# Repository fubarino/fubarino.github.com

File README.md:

fubarino: Social Hardware and Software
========
Main Project Pages are:
http://fubarino.org

The chipKIT Fubarino SD board brings affordable, breadboard compatible high speed computing power to the Arduino-compatible chipKIT/MPIDE platform. It is able to run almost all Arduino sketches right out of the box at a great price, and includes more memory, speed, and I/O pins than a typical Arduino or clone. And it includes a microSD card slot for easy sketch access to huge file storage.
chipKIT FubarinoSD
======
Class on a stick. Course materials can fit on the SD card. The device mounts as a USB device. Unfortunately, at 1.0 speeds. But 
it will cut 45 minutes of getting started to 15 minutes. When offering online course using electronics all the course materials can be placed on the board.

The goal with the project is two have two boards that are excellent for small, and bread boardable projects.

Social Hardware:
=====
* Open Source
* Open Hardware
* Sharable

Licensing
====
The chipKIT Fubarino SD hardware is licensed under the Solderpad Hardware License v0.5. All MPIDE source code is licensed under GPL or other open source software licenses.

Availability:
========
These boards are Open Source Hardware and all the files are managed in this project, and are licensed as OpenSource.

* Purchase Fubarino SD version 1.5 at [microchipDIRECT](http://www.microchipdirect.com/ProductSearch.aspx?Keywords=TCHIP010)
* Purchase Fubarino SD version 1.4 at [Seeed Studio](http://www.seeedstudio.com/depot/fubarino-sd-p-1265.html?cPath=132_133)
* Purchase Fubarino Mini version 1.5 at [microchipDIRECT](http://www.microchipdirect.com/ProductSearch.aspx?Keywords=TCHIP011)

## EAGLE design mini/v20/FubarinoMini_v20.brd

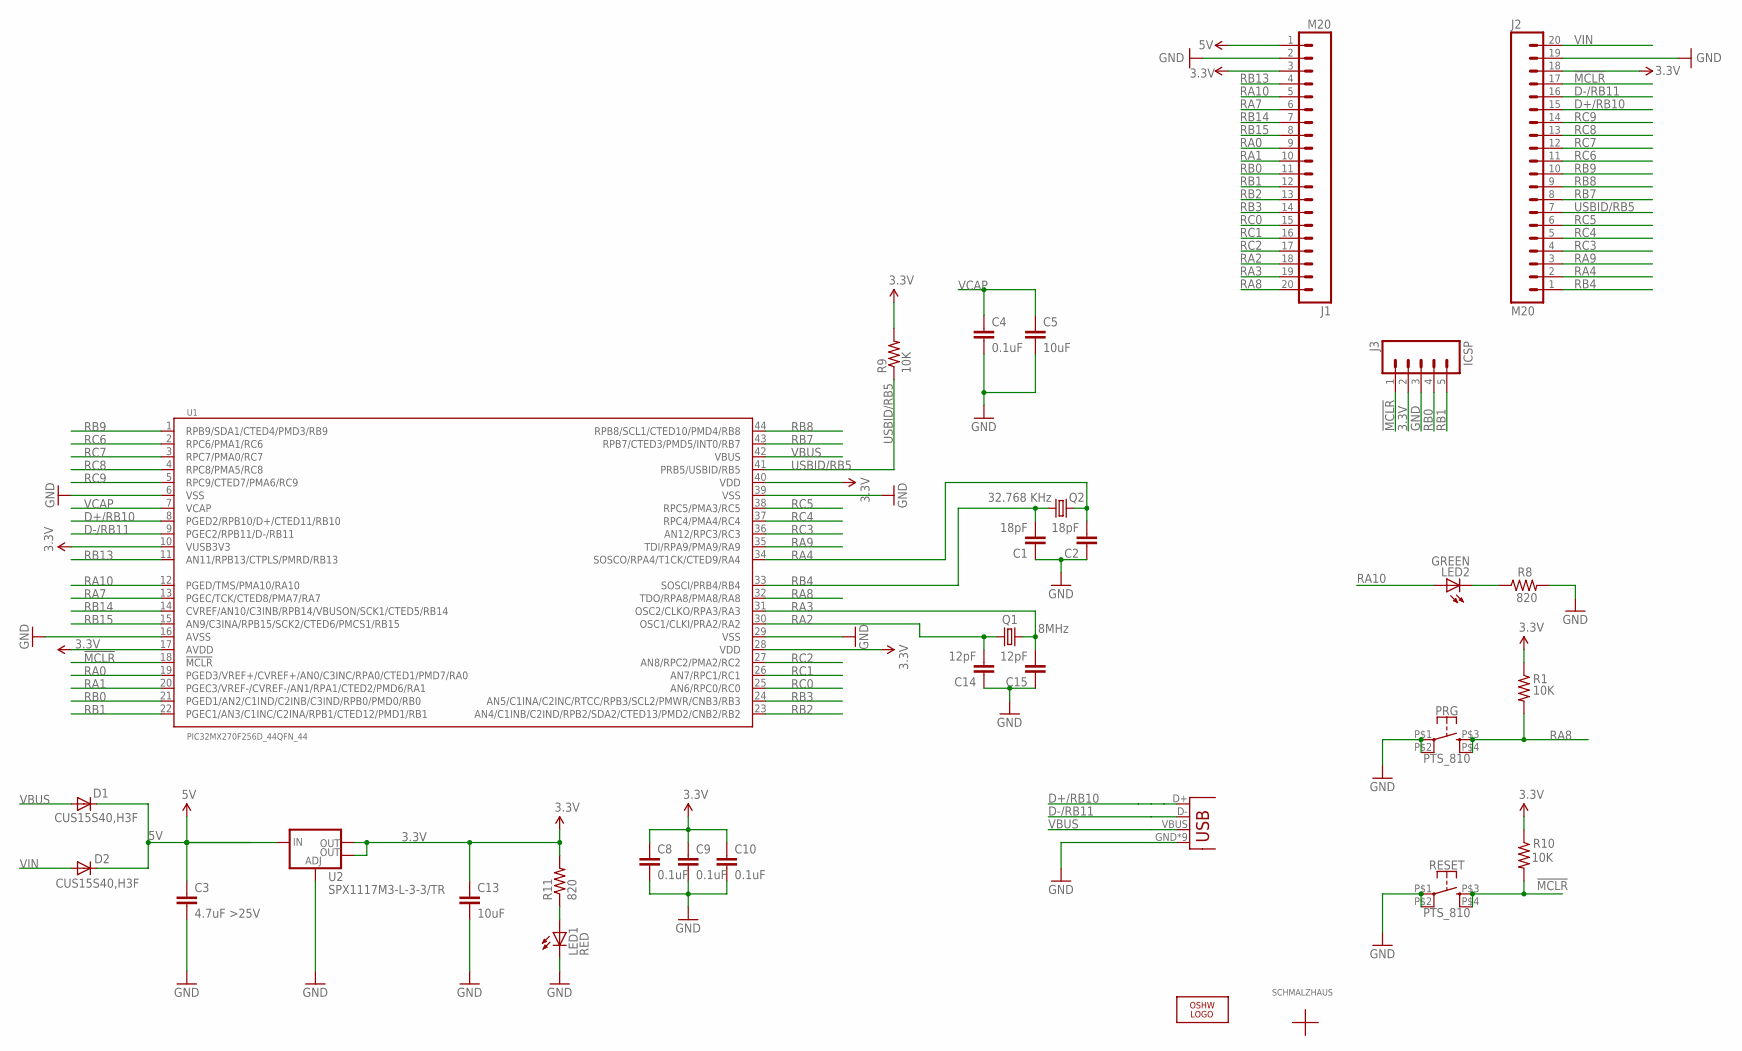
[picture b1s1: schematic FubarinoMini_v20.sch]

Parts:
C1, C2: 18pF; 0603-CAP
C3: 4.7uF >25V; 0603-CAP
C4, C8, C9: 0.1uF; 0603-CAP
C5, C13: 10uF; 0805
C10: 0.1uF; 0603
C14, C15: 12pF; 0603-CAP
D1, D2: CUS15S40,H3F; SOD-323
ICSP: J3; 1X05_NOSILK
J1, J2: M20; 1X20_NO_PIN1
LED1: RED; LED-0603
LED2: GREEN; LED-0603
LOGO1: OSHW_LOGO_8MILX0070-NT; OSHW_8X70_NOTEXT
PRG: PTS_810
Q1: 8MHz; NX3225GD
Q2: 32.768 KHz; TC26H
R1, R9, R10: 10K; 0603-RES
R8, R11: 820; 0603-RES
RESET: PTS_810
U1: PIC32MX270F256D_44QFN_44; QFN-44-8X8-NOPAD
U2: SPX1117M3-L-3-3/TR; SOT223
U$1: SCHMALZHAUSSCHMALZHAUS_SMALL; SCHMALZHAUS_SMALL
U$2: CE_MARK5MM; CE_5MM
U$3: ROSH_GARBAGE; ROHS_GARBAGE_5MM
U$4: CHIPKIT2MM; CHIPKIT_2MM
U$5: USBMICROB; USB-MICROB_FCI_PINS

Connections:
3.3V: C8.1, C9.1, C10.1, C13.1, ICSP.2, J1.3, J2.18, R1.1, R9.2, R10.1, R11.2, U1.10 (VUSB3V3), U1.17 (AVDD), U1.28 (VDD), U1.40 (VDD), U2.2 (OUT), U2.4 (OUT)
5V: C3.1, D1.1 (C), D2.1 (C), J1.1, U2.3 (IN)
!MCLR!: ICSP.1, J2.17, R10.2, RESET.P$3 (3), RESET.P$4 (4), U1.18 (!MCLR!)
D+/RB10: J2.15, U1.8 (PGED2/RPB10/D+/CTED11/RB10), U$5.D+
D-/RB11: J2.16, U1.9 (PGEC2/RPB11/D-/RB11), U$5.D-
GND: C1.1, C2.1, C3.2, C4.2, C5.2, C8.2, C9.2, C10.2, C13.2, C14.1, C15.1, ICSP.3, J1.2, J2.19, LED1.C, PRG.P$1 (1), PRG.P$2 (2), R8.2, RESET.P$1 (1), RESET.P$2 (2), U1.6 (VSS), U1.16 (AVSS), U1.29 (VSS), U1.39 (VSS), U2.1 (ADJ), U$5.GND, U$5.GND@1 (GND), U$5.GND@2 (GND), U$5.GND@3 (GND), U$5.GND@4 (GND), U$5.GND@5 (GND), U$5.GND@6 (GND), U$5.GND@7 (GND), U$5.GND@8 (GND)
unnamed: LED1.A, R11.1
unnamed: LED2.C, R8.1
RA0: J1.9, U1.19 (PGED3/VREF+/CVREF+/AN0/C3INC/RPA0/CTED1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)
RA1: J1.10, U1.20 (PGEC3/VREF-/CVREF-/AN1/RPA1/CTED2/PMD6/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)
RA2: C14.2, J1.18, Q1.P$1 (1), U1.30 (OSC1/CLKI/PRA2/RA2)
RA3: C15.2, J1.19, Q1.P$2 (2), U1.31 (OSC2/CLKO/RPA3/RA3)
RA4: C2.2, J2.2, Q2.1, U1.34 (SOSCO/RPA4/T1CK/CTED9/RA4)
RA7: J1.6, U1.13 (PGEC/TCK/CTED8/PMA7/RA7)
RA8: J1.20, PRG.P$3 (3), PRG.P$4 (4), R1.2, U1.32 (TDO/RPA8/PMA8/RA8)
RA9: J2.3, U1.35 (TDI/RPA9/PMA9/RA9)
RA10: J1.5, LED2.A, U1.12 (PGED/TMS/PMA10/RA10)
RB0: ICSP.4, J1.11, U1.21 (PGED1/AN2/C1IND/C2INB/C3IND/RPB0/PMD0/R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)
RB1: ICSP.5, J1.12, U1.22 (PGEC1/AN3/C1INC/C2INA/RPB1/CTED12/PMD1/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)
RB2: J1.13, U1.23 (AN4/C1INB/C2IND/RPB2/SDA2/CTED13/PMD2/C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)
RB3: J1.14, U1.24 (AN5/C1INA/C2INC/RTCC/RPB3/SCL2/PMWR/CNB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)
RB4: C1.2, J2.1, Q2.2, U1.33 (SOSCI/PRB4/RB4)
RB7: J2.8, U1.43 (RPB7/CTED3/PMD5/INT0/RB7)
RB8: J2.9, U1.44 (RPB8/SCL1/CTED10/PMD4/RB8)
RB9: J2.10, U1.1 (RPB9/SDA1/CTED4/PMD3/RB9)
RB13: J1.4, U1.11 (AN11/RPB13/CTPLS/PMRD/RB13)
RB14: J1.7, U1.14 (CVREF/AN10/C3INB/RPB14/VBUSON/SCK1/CTED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)
RB15: J1.8, U1.15 (AN9/C3INA/RPB15/SCK2/CTED6/PMCS1/RB15)
RC0: J1.15, U1.25 (AN6/RPC0/RC0)
RC1: J1.16, U1.26 (AN7/RPC1/RC1)
RC2: J1.17, U1.27 (AN8/RPC2/PMA2/RC2)
RC3: J2.4, U1.36 (AN12/RPC3/RC3)
RC4: J2.5, U1.37 (RPC4/PMA4/RC4)
RC5: J2.6, U1.38 (RPC5/PMA3/RC5)
RC6: J2.11, U1.2 (RPC6/PMA1/RC6)
RC7: J2.12, U1.3 (RPC7/PMA0/RC7)
RC8: J2.13, U1.4 (RPC8/PMA5/RC8)
RC9: J2.14, U1.5 (RPC9/CTED7/PMA6/RC9)
USBID/RB5: J2.7, R9.1, U1.41 (PRB5/USBID/RB5)
VBUS: D1.2 (A), U1.42 (VBUS), U$5.VBUS
VCAP: C4.1, C5.1, U1.7 (VCAP)
VIN: D2.2 (A), J2.20

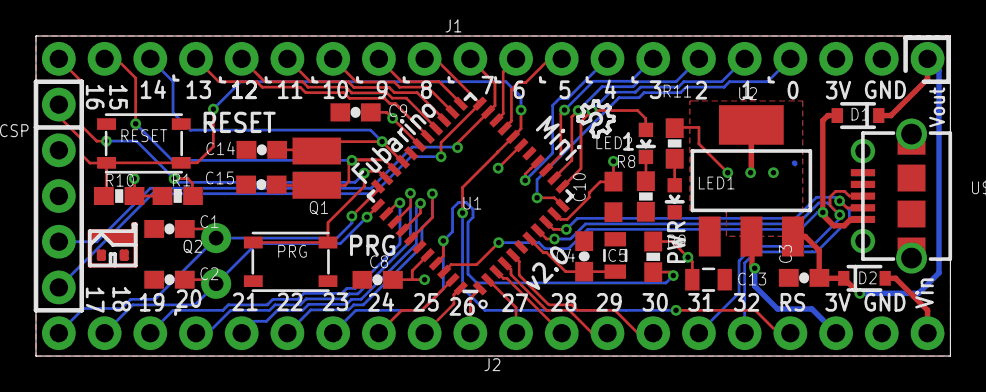
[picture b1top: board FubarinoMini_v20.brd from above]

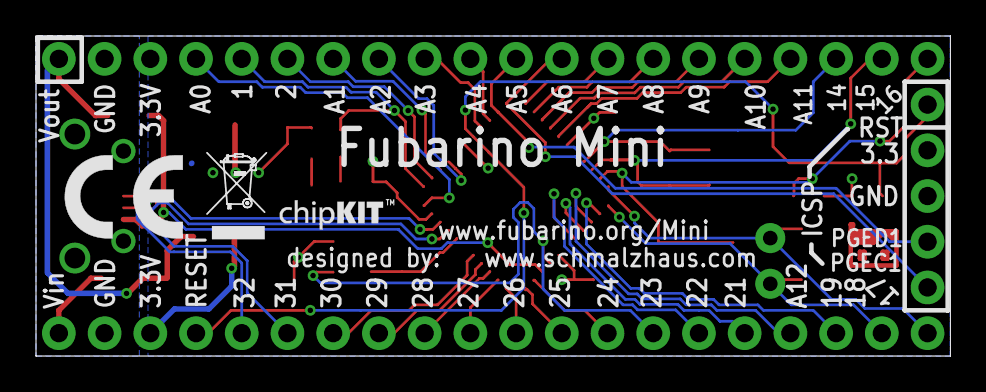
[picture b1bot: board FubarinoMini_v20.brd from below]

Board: 2 copper layers, 50.8 x 17.8 mm, 36 parts (3 on the bottom side), 42 nets.

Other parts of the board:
DRILEGEND: DRILEGEND

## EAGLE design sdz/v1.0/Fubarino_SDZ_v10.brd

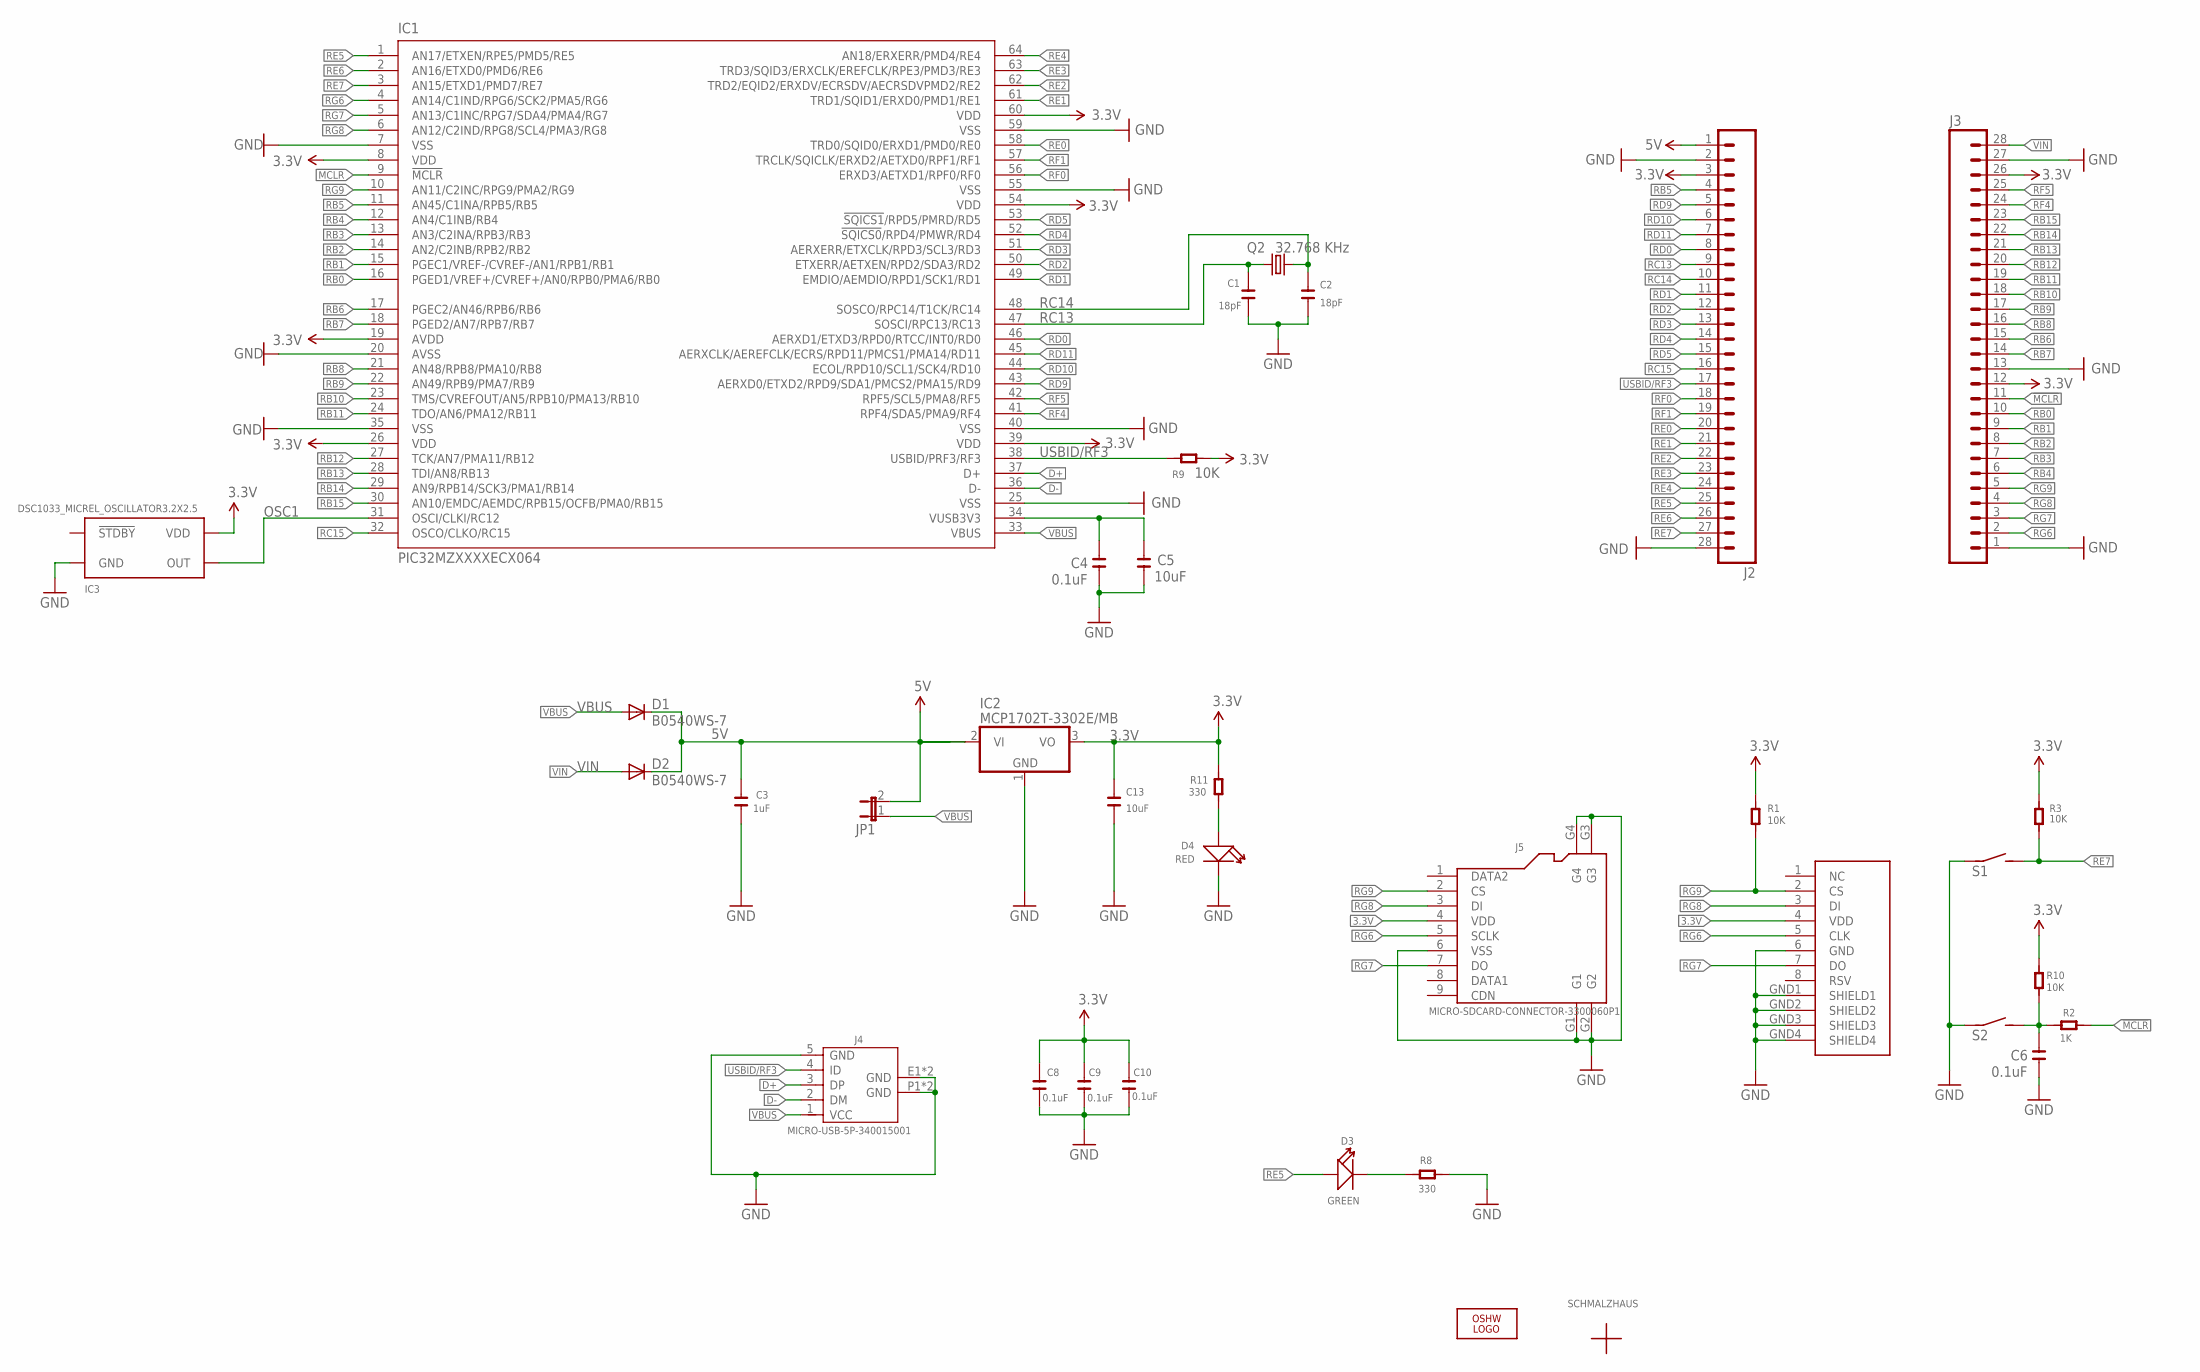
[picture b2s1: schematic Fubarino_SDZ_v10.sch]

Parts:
C1, C2: 18pF; C0603
C3: 1uF; C0603
C4, C6, C8, C9, C10: 0.1uF; C0603
C5, C13: 10uF; C0805
D1, D2: B0540WS-7; SOD-323
D3: GREEN; LED0603
D4: RED; LED0603
IC1: PIC32MZXXXXECX064; TQFP64-10X10
IC2: MCP1702T-3302E/MB; SOT89
IC3: DSC1033_MICREL_OSCILLATOR3.2X2.5; 3.2X2.5_SILABS_OSC_DSC1033
J1: MICRO_SD_CARD_SOCKET; SD-MMC_SOCKET-PP
J2: M28USEPIN1; 1X28
J3: M28NOPIN1; 1X28_NO_PIN_1
J4: MICRO-USB-5P-340015001; B-SMD-5P
J5: MICRO-SDCARD-CONNECTOR-3300060P1; 9P-SMD-W-RING
JP1: JUMPER-2SMD-NO; SJ_2S-NO
LOGO1: OSHW_LOGO_8MILX0070-NT; OSHW_8X70_NOTEXT
Q2: 32.768 KHz; TC26H
R1, R3, R9, R10: 10K; R0603
R2: 1K; R0603
R8, R11: 330; R0603
S1, S2: SWITCH; SWITCH_KMR_SMT_TACT
U$1: SCHMALZHAUSSCHMALZHAUS_SMALL; SCHMALZHAUS_SMALL
U$2: CE_MARK5MM; CE_5MM
U$3: ROHS_GARBAGE; ROHS_GARBAGE_5MM
U$4, U$5: CHIPKIT2MM; CHIPKIT_2MM

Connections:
3.3V: C8.1, C9.1, C10.1, C13.1, IC1.8 (VDD), IC1.19 (AVDD), IC1.26 (VDD), IC1.39 (VDD), IC1.54 (VDD), IC1.60 (VDD), IC2.3 (VO), IC3.P$4 (VDD), J1.4 (VDD), J2.3, J3.12, J3.26, J5.4 (VDD), R1.1, R3.1, R9.2, R10.1, R11.2
5V: C3.1, D1.1 (C), D2.1 (C), IC2.2 (VI), IC2.2@1 (VI1), J2.1, JP1.2
!MCLR!: IC1.9 (!MCLR!), J3.11, R2.2
$MCLR: C6.1, R2.1, R10.2, S2.P$3 (2), S2.P$4 (2)
D+: IC1.37 (D+), J4.3 (DP)
D-: IC1.36 (D-), J4.2 (DM)
GND: C1.1, C2.1, C3.2, C4.2, C5.2, C6.2, C8.2, C9.2, C10.2, C13.2, D4.-, IC1.7 (VSS), IC1.20 (AVSS), IC1.25 (VSS), IC1.35 (VSS), IC1.40 (VSS), IC1.55 (VSS), IC1.59 (VSS), IC2.1 (GND), IC3.P$2 (GND), J1.6 (GND), J1.GND1 (SHIELD1), J1.GND2 (SHIELD2), J1.GND3 (SHIELD3), J1.GND4 (SHIELD4), J2.2, J2.28, J3.1, J3.13, J3.27, J4.5 (GND), J4.E1 (GND), J4.E2 (GND), J4.P1 (GND), J4.P2 (GND), J5.6 (VSS), J5.G1, J5.G2, J5.G3, J5.G4, R8.2, S1.P$1 (1), S1.P$2 (1), S2.P$1 (1), S2.P$2 (1)
unnamed: D4.+, R11.1
unnamed: D3.-, R8.1
unnamed: C4.1, C5.1, IC1.34 (VUSB3V3)
OSC1: IC1.31 (OSCI/CLKI/RC12), IC3.P$3 (OUT)
RB0: IC1.16 (PGED1/VREF+/CVREF+/AN0/RPB0/PMA6/RB0), J3.10
RB1: IC1.15 (PGEC1/VREF-/CVREF-/AN1/RPB1/RB1), J3.9
RB2: IC1.14 (AN2/C2INB/RPB2/RB2), J3.8
RB3: IC1.13 (AN3/C2INA/RPB3/RB3), J3.7
RB4: IC1.12 (AN4/C1INB/RB4), J3.6
RB5: IC1.11 (AN45/C1INA/RPB5/RB5), J2.4
RB6: IC1.17 (PGEC2/AN46/RPB6/RB6), J3.15
RB7: IC1.18 (PGED2/AN7/RPB7/RB7), J3.14
RB8: IC1.21 (AN48/RPB8/PMA10/RB8), J3.16
RB9: IC1.22 (AN49/RPB9/PMA7/RB9), J3.17
RB10: IC1.23 (TMS/CVREFOUT/AN5/RPB10/PMA13/RB10), J3.18
RB11: IC1.24 (TDO/AN6/PMA12/RB11), J3.19
RB12: IC1.27 (TCK/AN7/PMA11/RB12), J3.20
RB13: IC1.28 (TDI/AN8/RB13), J3.21
RB14: IC1.29 (AN9/RPB14/SCK3/PMA1/RB14), J3.22
RB15: IC1.30 (AN10/EMDC/AEMDC/RPB15/OCFB/PMA0/RB15), J3.23
RC13: C1.2, IC1.47 (SOSCI/RPC13/RC13), J2.9, Q2.1
RC14: C2.2, IC1.48 (SOSCO/RPC14/T1CK/RC14), J2.10, Q2.2
RC15: IC1.32 (OSCO/CLKO/RC15), J2.16
RD0: IC1.46 (AERXD1/ETXD3/RPD0/RTCC/INT0/RD0), J2.8
RD1: IC1.49 (EMDIO/AEMDIO/RPD1/SCK1/RD1), J2.11
RD2: IC1.50 (ETXERR/AETXEN/RPD2/SDA3/RD2), J2.12
RD3: IC1.51 (AERXERR/ETXCLK/RPD3/SCL3/RD3), J2.13
RD4: IC1.52 (!SQICS0!/RPD4/PMWR/RD4), J2.14
RD5: IC1.53 (!SQICS1!/RPD5/PMRD/RD5), J2.15
RD9: IC1.43 (AERXD0/ETXD2/RPD9/SDA1/PMCS2/PMA15/RD9), J2.5
RD10: IC1.44 (ECOL/RPD10/SCL1/SCK4/RD10), J2.6
RD11: IC1.45 (AERXCLK/AEREFCLK/ECRS/RPD11/PMCS1/PMA14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), J2.7
RE0: IC1.58 (TRD0/SQID0/ERXD1/PMD0/RE0), J2.20
RE1: IC1.61 (TRD1/SQID1/ERXD0/PMD1/RE1), J2.21
RE2: IC1.62 (TRD2/EQID2/ERXDV/ECRSDV/AECRSDVPMD2/RE2), J2.22
RE3: IC1.63 (TRD3/SQID3/ERXCLK/EREFCLK/RPE3/PMD3/RE3), J2.23
RE4: IC1.64 (AN18/ERXERR/PMD4/RE4), J2.24
RE5: D3.+, IC1.1 (AN17/ETXEN/RPE5/PMD5/RE5), J2.25
RE6: IC1.2 (AN16/ETXD0/PMD6/RE6), J2.26
RE7: IC1.3 (AN15/ETXD1/PMD7/RE7), J2.27, R3.2, S1.P$3 (2), S1.P$4 (2)
RF0: IC1.56 (ERXD3/AETXD1/RPF0/RF0), J2.18
RF1: IC1.57 (TRCLK/SQICLK/ERXD2/AETXD0/RPF1/RF1), J2.19
RF4: IC1.41 (RPF4/SDA5/PMA9/RF4), J3.24
RF5: IC1.42 (RPF5/SCL5/PMA8/RF5), J3.25
RG6: IC1.4 (AN14/C1IND/RPG6/SCK2/PMA5/RG6), J1.5 (CLK), J3.2, J5.5 (SCLK)
RG7: IC1.5 (AN13/C1INC/RPG7/SDA4/PMA4/RG7), J1.7 (DO), J3.3, J5.7 (DO)
RG8: IC1.6 (AN12/C2IND/RPG8/SCL4/PMA3/RG8), J1.3 (DI), J3.4, J5.3 (DI)
RG9: IC1.10 (AN11/C2INC/RPG9/PMA2/RG9), J1.2 (CS), J3.5, J5.2 (CS), R1.2
USBID/RF3: IC1.38 (USBID/PRF3/RF3), J2.17, J4.4 (ID), R9.1
VBUS: D1.2 (A), IC1.33 (VBUS), J4.1 (VCC), JP1.1
VIN: D2.2 (A), J3.28

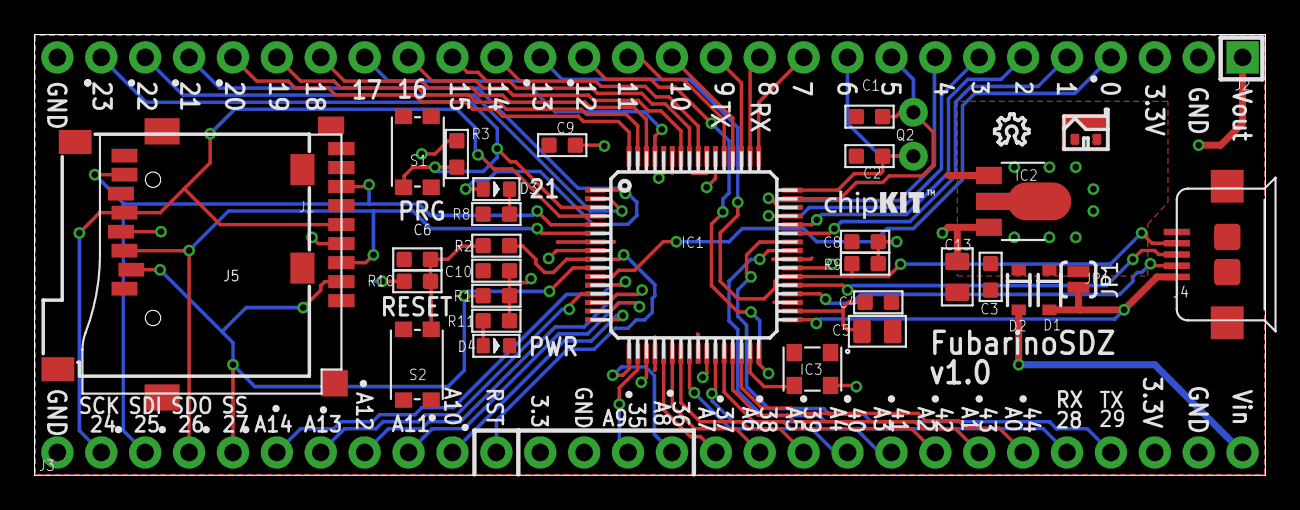
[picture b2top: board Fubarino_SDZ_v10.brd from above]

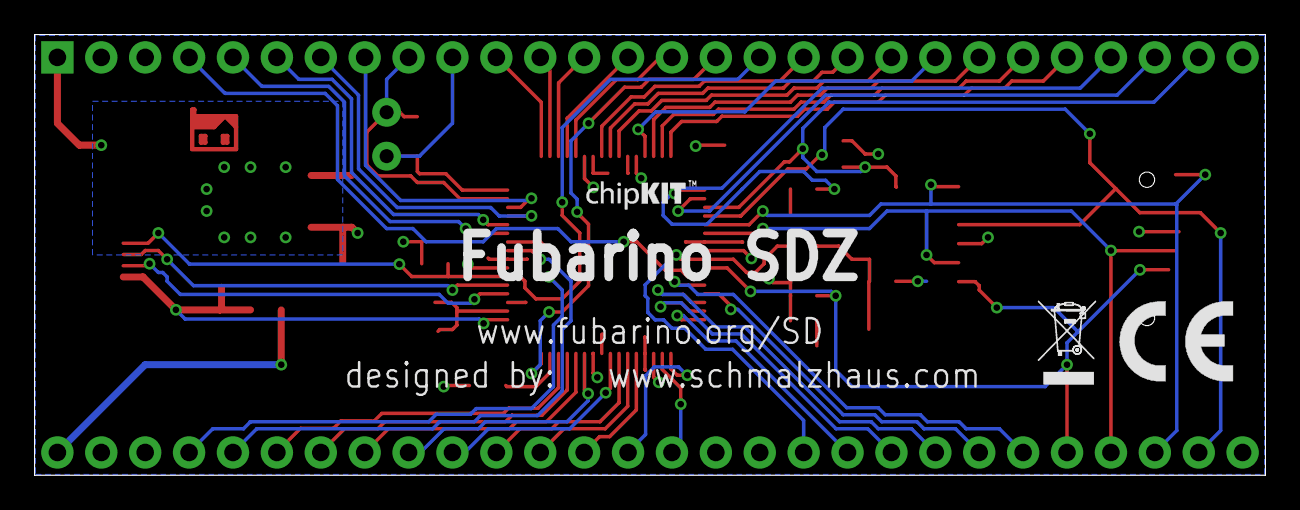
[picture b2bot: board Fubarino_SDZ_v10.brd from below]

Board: 2 copper layers, 71.2 x 25.5 mm, 40 parts (3 on the bottom side), 58 nets.

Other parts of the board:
DRILEGEND: DRILEGEND

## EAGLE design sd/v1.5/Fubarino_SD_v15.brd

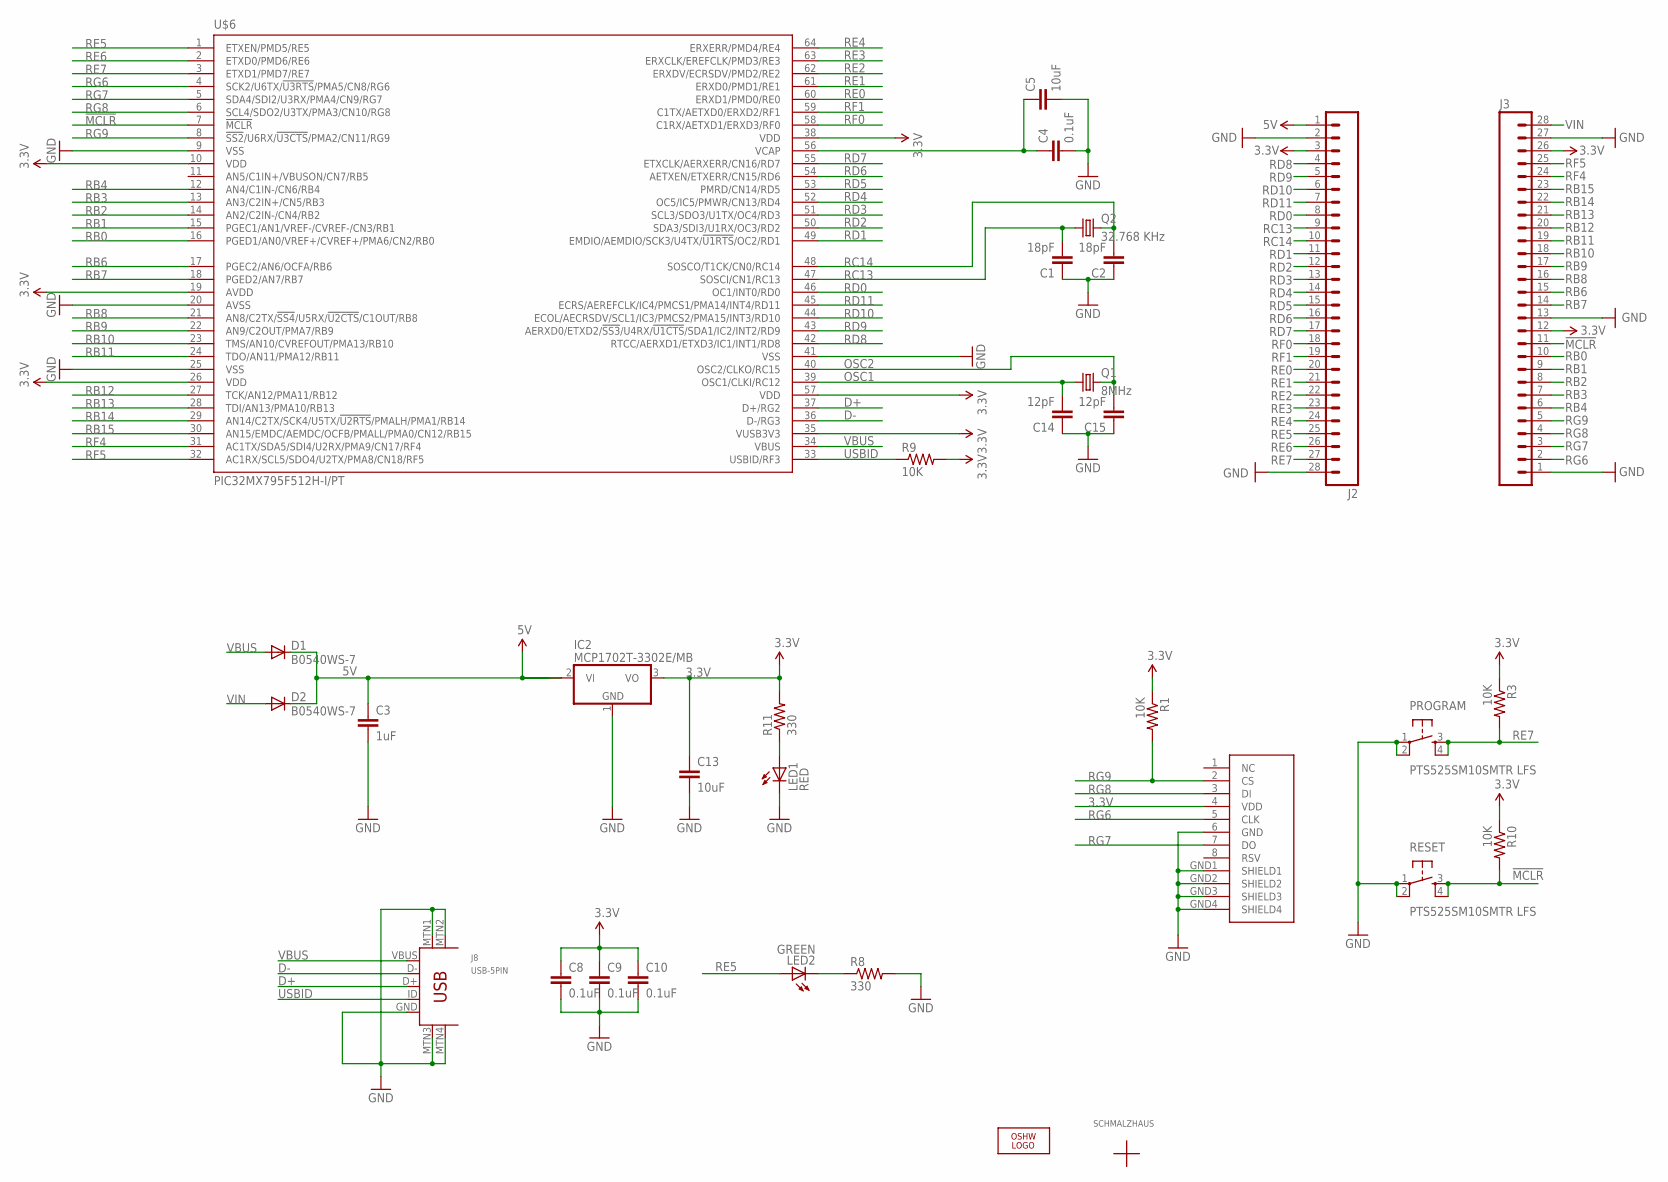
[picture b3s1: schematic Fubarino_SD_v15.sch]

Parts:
C1, C2: 18pF; 0603-CAP
C3: 1uF; 0603-CAP
C4, C8, C9: 0.1uF; 0603-CAP
C5, C13: 10uF; 0805
C10: 0.1uF; 0603
C14, C15: 12pF; 0603-CAP
D1, D2: B0540WS-7; SOD-323
IC2: MCP1702T-3302E/MB; SOT89
J1: MICRO_SD_CARD_SOCKET; SD-MMC_SOCKET-PP
J2: M28USEPIN1; 1X28
J3: M28NOPIN1; 1X28_NO_PIN_1
J8: USB-5PIN; USB-MINIB-5PIN-HIROSE-UX60-MB-5ST
LED1: RED; LED-0603
LED2: GREEN; LED-0603
LOGO1: OSHW_LOGO_8MILX0070-NT; OSHW_8X70_NOTEXT
PROGRAM: PTS525SM10SMTR LFS; TACTILE_SWITCH_SMD
Q1: 8MHz; NX5032_5MM_3.2MM_CRYSTAL
Q2: 32.768 KHz; TC26H
R1, R3, R9, R10: 10K; 0603-RES
R8, R11: 330; 0603-RES
RESET: PTS525SM10SMTR LFS; TACTILE_SWITCH_SMD
U$1: SCHMALZHAUSSCHMALZHAUS_SMALL; SCHMALZHAUS_SMALL
U$2: CE_MARK5MM; CE_5MM
U$3: ROHS_GARBAGE; ROHS_GARBAGE_5MM
U$4, U$5: CHIPKIT2MM; CHIPKIT_2MM
U$6: PIC32MX795F512H-I/PT; TQFP64-10X10

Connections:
3.3V: C8.1, C9.1, C10.1, C13.1, IC2.3 (VO), J1.4 (VDD), J2.3, J3.12, J3.26, R1.1, R3.1, R9.2, R10.1, R11.2, U$6.10 (VDD), U$6.19 (AVDD), U$6.26 (VDD), U$6.35 (VUSB3V3), U$6.38 (VDD), U$6.57 (VDD)
5V: C3.1, D1.1 (C), D2.1 (C), IC2.2 (VI), IC2.2@1 (VI1), J2.1
!MCLR!: J3.11, R10.2, RESET.3, RESET.4, U$6.7 (!MCLR)
D+: J8.D+, U$6.37 (D+/RG2)
D-: J8.D-, U$6.36 (D-/RG3)
GND: C1.1, C2.1, C3.2, C4.2, C5.2, C8.2, C9.2, C10.2, C13.2, C14.1, C15.1, IC2.1 (GND), J1.6 (GND), J1.GND1 (SHIELD1), J1.GND2 (SHIELD2), J1.GND3 (SHIELD3), J1.GND4 (SHIELD4), J2.2, J2.28, J3.1, J3.13, J3.27, J8.GND, J8.MTN1, J8.MTN2, J8.MTN3, J8.MTN4, LED1.C, PROGRAM.1, PROGRAM.2, R8.2, RESET.1, RESET.2, U$6.9 (VSS), U$6.20 (AVSS), U$6.25 (VSS), U$6.41 (VSS)
unnamed: LED1.A, R11.1
unnamed: LED2.C, R8.1
unnamed: C4.1, C5.1, U$6.56 (VCAP)
OSC1: C14.2, Q1.1, U$6.39 (OSC1/CLKI/RC12)
OSC2: C15.2, Q1.2, U$6.40 (OSC2/CLKO/RC15)
RB0: J3.10, U$6.16 (PGED1/AN0/VREF+/CVREF+/PMA6/CN2/RB0)
RB1: J3.9, U$6.15 (PGEC1/AN1/VREF-/CVREF-/CN3/RB1)
RB2: J3.8, U$6.14 (AN2/C2IN-/CN4/RB2)
RB3: J3.7, U$6.13 (AN3/C2IN+/CN5/RB3)
RB4: J3.6, U$6.12 (AN4/C1IN-/CN6/RB4)
RB6: J3.15, U$6.17 (PGEC2/AN6/OCFA/RB6)
RB7: J3.14, U$6.18 (PGED2/AN7/RB7)
RB8: J3.16, U$6.21 (AN8/C2TX/!SS4!/U5RX/!U2CTS!/C1OUT/RB8)
RB9: J3.17, U$6.22 (AN9/C2OUT/PMA7/RB9)
RB10: J3.18, U$6.23 (TMS/AN10/CVREFOUT/PMA13/RB10)
RB11: J3.19, U$6.24 (TDO/AN11/PMA12/RB11)
RB12: J3.20, U$6.27 (TCK/AN12/PMA11/RB12)
RB13: J3.21, U$6.28 (TDI/AN13/PMA10/RB13)
RB14: J3.22, U$6.29 (AN14/C2TX/SCK4/U5TX/!U2RTS!/PMALH/PMA1/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)
RB15: J3.23, U$6.30 (AN15/EMDC/AEMDC/OCFB/PMALL/PMA0/CN12/RB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)
RC13: C1.2, J2.9, Q2.1, U$6.47 (SOSCI/CN1/RC13)
RC14: C2.2, J2.10, Q2.2, U$6.48 (SOSCO/T1CK/CN0/RC14)
RD0: J2.8, U$6.46 (OC1/INT0/RD0)
RD1: J2.11, U$6.49 (EMDIO/AEMDIO/SCK3/U4TX/!U1RTS!/OC2/RD1)
RD2: J2.12, U$6.50 (SDA3/SDI3/U1RX/OC3/RD2)
RD3: J2.13, U$6.51 (SCL3/SDO3/U1TX/OC4/RD3)
RD4: J2.14, U$6.52 (OC5/IC5/PMWR/CN13/RD4)
RD5: J2.15, U$6.53 (PMRD/CN14/RD5)
RD6: J2.16, U$6.54 (AETXEN/ETXERR/CN15/RD6)
RD7: J2.17, U$6.55 (ETXCLK/AERXERR/CN16/RD7)
RD8: J2.4, U$6.42 (RTCC/AERXD1/ETXD3/IC1/INT1/RD8)
RD9: J2.5, U$6.43 (AERXD0/ETXD2/!SS3!/U4RX/!U1CTS!/SDA1/IC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)
RD10: J2.6, U$6.44 (ECOL/AECRSDV/SCL1/IC3/PMCS2/PMA15/INT3/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)
RD11: J2.7, U$6.45 (ECRS/AEREFCLK/IC4/PMCS1/PMA14/INT4/RD11)
RE0: J2.20, U$6.60 (ERXD1/PMD0/RE0)
RE1: J2.21, U$6.61 (ERXD0/PMD1/RE1)
RE2: J2.22, U$6.62 (ERXDV/ECRSDV/PMD2/RE2)
RE3: J2.23, U$6.63 (ERXCLK/EREFCLK/PMD3/RE3)
RE4: J2.24, U$6.64 (ERXERR/PMD4/RE4)
RE5: J2.25, LED2.A, U$6.1 (ETXEN/PMD5/RE5)
RE6: J2.26, U$6.2 (ETXD0/PMD6/RE6)
RE7: J2.27, PROGRAM.3, PROGRAM.4, R3.2, U$6.3 (ETXD1/PMD7/RE7)
RF0: J2.18, U$6.58 (C1RX/AETXD1/ERXD3/RF0)
RF1: J2.19, U$6.59 (C1TX/AETXD0/ERXD2/RF1)
RF4: J3.24, U$6.31 (AC1TX/SDA5/SDI4/U2RX/PMA9/CN17/RF4)
RF5: J3.25, U$6.32 (AC1RX/SCL5/SDO4/U2TX/PMA8/CN18/RF5)
RG6: J1.5 (CLK), J3.2, U$6.4 (SCK2/U6TX/!U3RTS!/PMA5/CN8/RG6)
RG7: J1.7 (DO), J3.3, U$6.5 (SDA4/SDI2/U3RX/PMA4/CN9/RG7)
RG8: J1.3 (DI), J3.4, U$6.6 (SCL4/SDO2/U3TX/PMA3/CN10/RG8)
RG9: J1.2 (CS), J3.5, R1.2, U$6.8 (!SS2!/U6RX/!U3CTS!/PMA2/CN11/RG9)
USBID: J8.ID, R9.1, U$6.33 (USBID/RF3)
VBUS: D1.2 (A), J8.VBUS, U$6.34 (VBUS)
VIN: D2.2 (A), J3.28

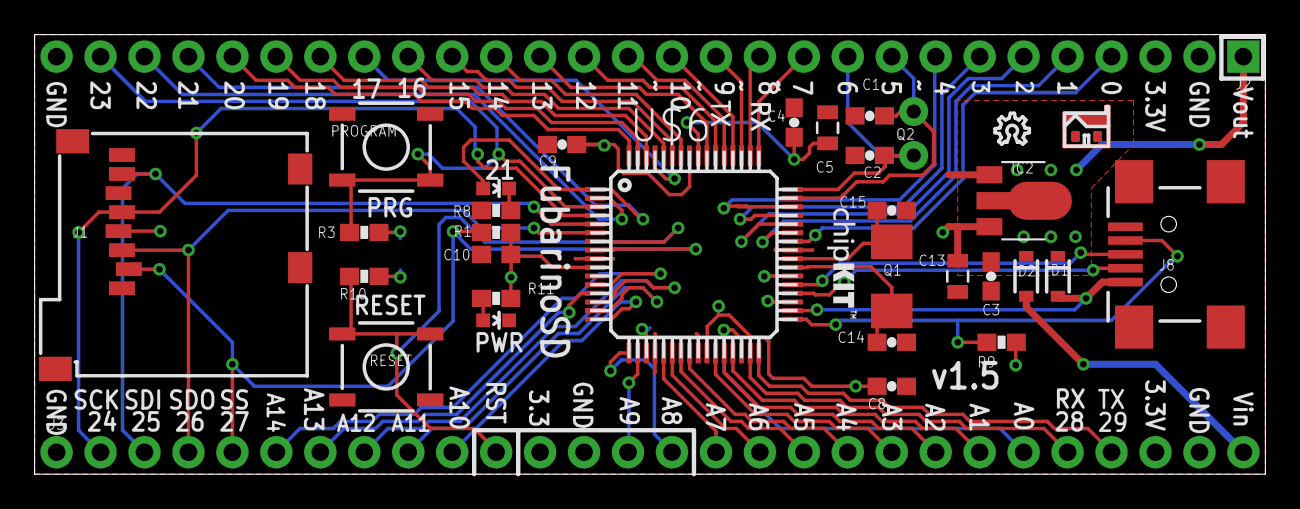
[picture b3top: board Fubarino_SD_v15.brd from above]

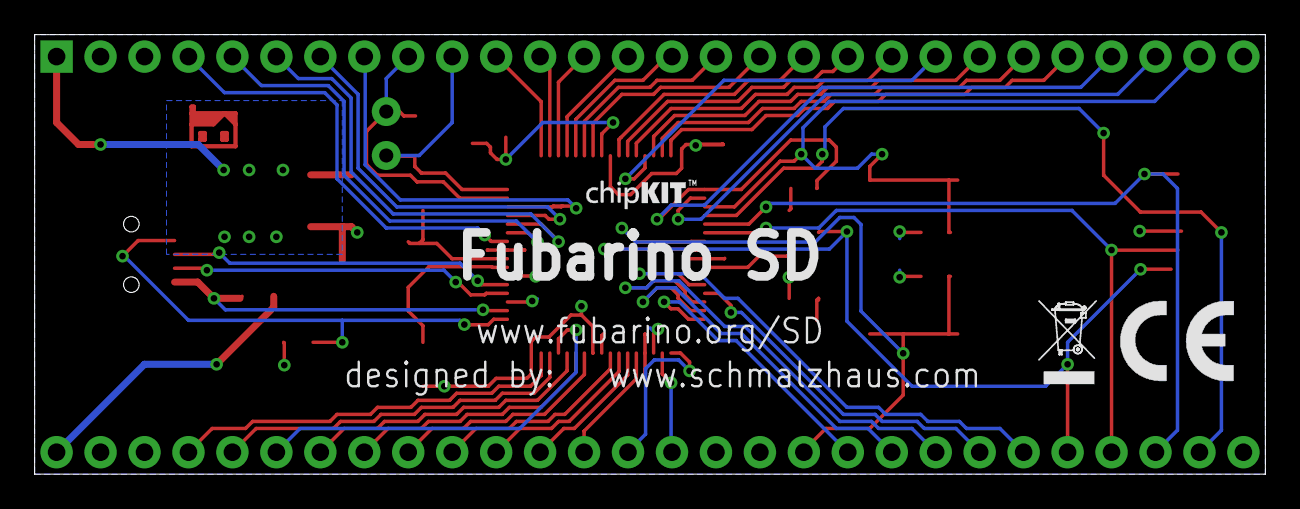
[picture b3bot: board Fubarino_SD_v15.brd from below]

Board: 2 copper layers, 71.1 x 25.4 mm, 38 parts (3 on the bottom side), 59 nets.

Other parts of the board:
DRILEGEND: DRILEGEND

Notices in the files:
rawfiles/fubarinov1_1verygoodnews/Fubarino_v11/Board_Data.c:
Copyright 2011, Digilent. All rights reserved
Copyright (c) 2010, 2011 by Mark Sproul
Copyright (c) 2005, 2006 by David A. Mellis
Public License along with this library; if not, write to the
Free Software Foundation, Inc., 59 Temple Place, Suite 330,
Boston, MA  02111-1307  USA
accessories/FubarStep/FuabarStep_v13/FubarStep_v13.sch:
Copyright 2013 Brian Schmalz and Rick Anderson Copyright and related rights are licensed under the Solderpad Hardware License, Version 0.51 (the “License”);
